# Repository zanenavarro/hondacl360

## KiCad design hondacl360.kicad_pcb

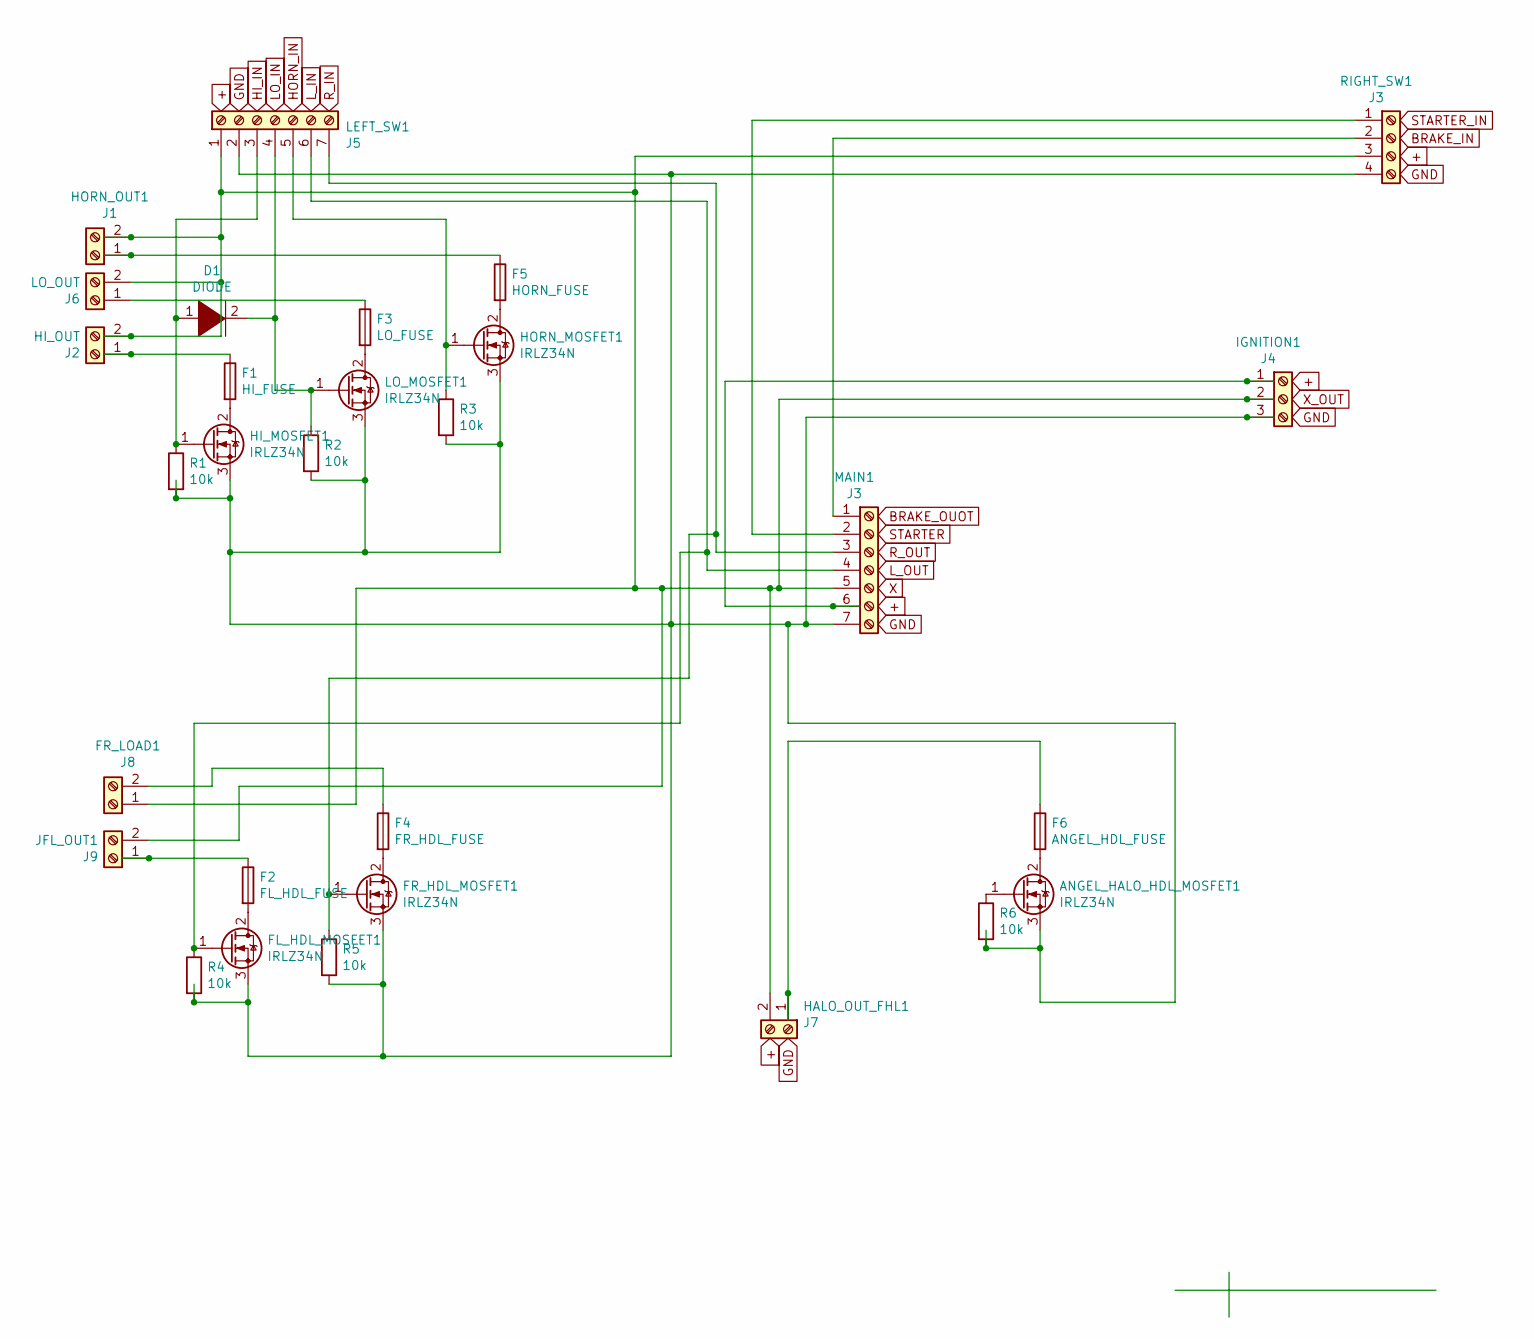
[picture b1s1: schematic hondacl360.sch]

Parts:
ANGEL_HALO_HDL_MOSFET1: IRLZ34N; TO-220-3_Vertical
D1: DIODE; D_DO-35_SOD27_P2.54mm_Vertical_AnodeUp
F1: HI_FUSE; Fuseholder_Blade_Mini_Keystone_3568
F2: FL_HDL_FUSE; Fuseholder_Blade_Mini_Keystone_3568
F3: LO_FUSE; Fuseholder_Blade_Mini_Keystone_3568
F4: FR_HDL_FUSE; Fuseholder_Blade_Mini_Keystone_3568
F5: HORN_FUSE; Fuseholder_Blade_Mini_Keystone_3568
F6: ANGEL_HDL_FUSE; Fuseholder_Blade_Mini_Keystone_3568
FL_HDL_MOSFET1: IRLZ34N; TO-220-3_Vertical
FR_HDL_MOSFET1: IRLZ34N; TO-220-3_Vertical
FR_LOAD1: J8; JST_GH_SM02B-GHS-TB_1x02-1MP_P1.25mm_Horizontal
HALO_OUT_FHL1: J7; JST_GH_SM02B-GHS-TB_1x02-1MP_P1.25mm_Horizontal
HI_MOSFET1: IRLZ34N; TO-220-3_Vertical
HORN_MOSFET1: IRLZ34N; TO-220-3_Vertical
HORN_OUT1: J1; JST_GH_SM02B-GHS-TB_1x02-1MP_P1.25mm_Horizontal
IGNITION1: J4; JST_GH_SM03B-GHS-TB_1x03-1MP_P1.25mm_Horizontal
J2: HI_OUT; JST_GH_SM02B-GHS-TB_1x02-1MP_P1.25mm_Horizontal
J6: LO_OUT; JST_GH_SM02B-GHS-TB_1x02-1MP_P1.25mm_Horizontal
JFL_OUT1: J9; JST_GH_SM02B-GHS-TB_1x02-1MP_P1.25mm_Horizontal
LEFT_SW1: J5; JST_GH_SM07B-GHS-TB_1x07-1MP_P1.25mm_Horizontal
LO_MOSFET1: IRLZ34N; TO-220-3_Vertical
MAIN1: J3; JST_XH_B7B-XH-A_1x07_P2.50mm_Vertical
R1, R2, R3, R4, R5, R6: 10k; R_Axial_DIN0204_L3.6mm_D1.6mm_P2.54mm_Vertical
RIGHT_SW1: J3; JST_GH_SM04B-GHS-TB_1x04-1MP_P1.25mm_Horizontal

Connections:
unnamed: ANGEL_HALO_HDL_MOSFET1.1 (G), R6.1
unnamed: ANGEL_HALO_HDL_MOSFET1.2 (D), F6.2
unnamed: ANGEL_HALO_HDL_MOSFET1.3 (S), FL_HDL_MOSFET1.3 (S), FR_HDL_MOSFET1.3 (S), HI_MOSFET1.3 (S), HORN_MOSFET1.3 (S), IGNITION1.3, LEFT_SW1.2, LO_MOSFET1.3 (S), MAIN1.7, R1.2, R2.2, R3.2, R4.2, R5.2, R6.2, RIGHT_SW1.4
unnamed: D1.1 (K), HI_MOSFET1.1 (G), LEFT_SW1.3, R1.1
unnamed: D1.2 (A), LEFT_SW1.4, LO_MOSFET1.1 (G), R2.1
unnamed: F1.1, J2.1
unnamed: F1.2, HI_MOSFET1.2 (D)
unnamed: F2.1, JFL_OUT1.1
unnamed: F2.2, FL_HDL_MOSFET1.2 (D)
unnamed: F3.1, J6.1
unnamed: F3.2, LO_MOSFET1.2 (D)
unnamed: F4.1, FR_LOAD1.2
unnamed: F4.2, FR_HDL_MOSFET1.2 (D)
unnamed: F5.1, HORN_OUT1.1
unnamed: F5.2, HORN_MOSFET1.2 (D)
unnamed: F6.1, HALO_OUT_FHL1.1
unnamed: FL_HDL_MOSFET1.1 (G), LEFT_SW1.6, MAIN1.4, R4.1
unnamed: FR_HDL_MOSFET1.1 (G), LEFT_SW1.7, MAIN1.3, R5.1
unnamed: FR_LOAD1.1, HALO_OUT_FHL1.2, HORN_OUT1.2, IGNITION1.2, J2.2, J6.2, JFL_OUT1.2, LEFT_SW1.1, MAIN1.5, RIGHT_SW1.3
unnamed: HORN_MOSFET1.1 (G), LEFT_SW1.5, R3.1
unnamed: IGNITION1.1, MAIN1.6
unnamed: MAIN1.1, RIGHT_SW1.2
unnamed: MAIN1.2, RIGHT_SW1.1

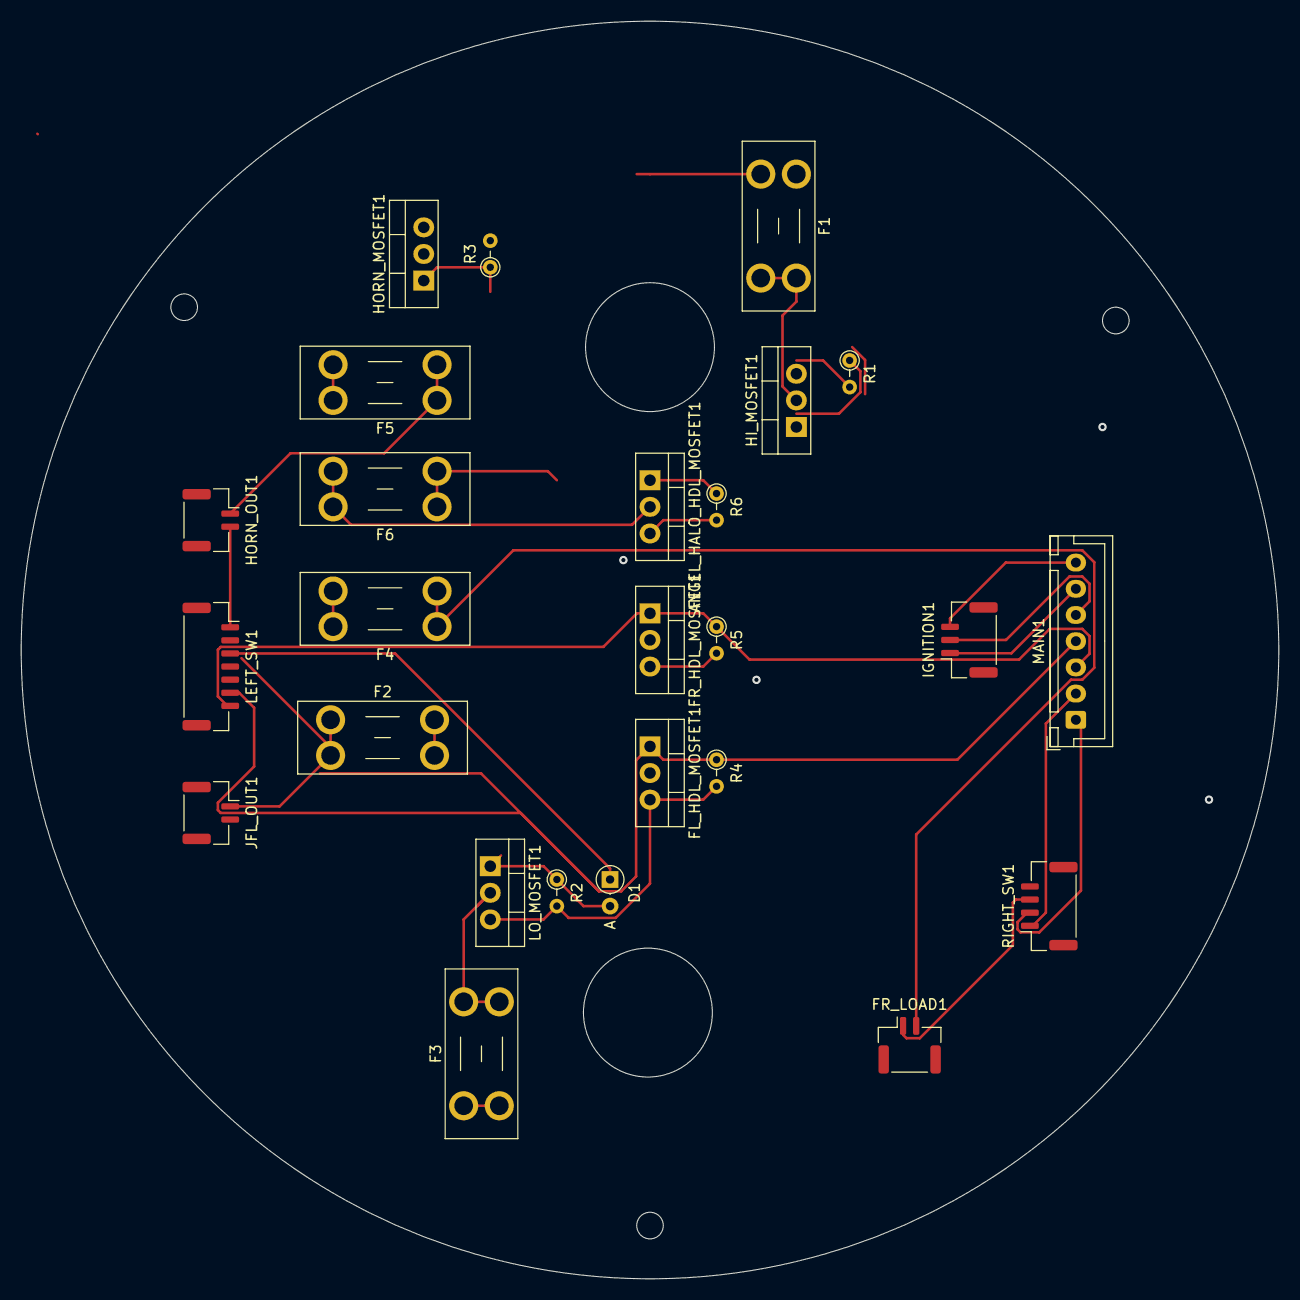
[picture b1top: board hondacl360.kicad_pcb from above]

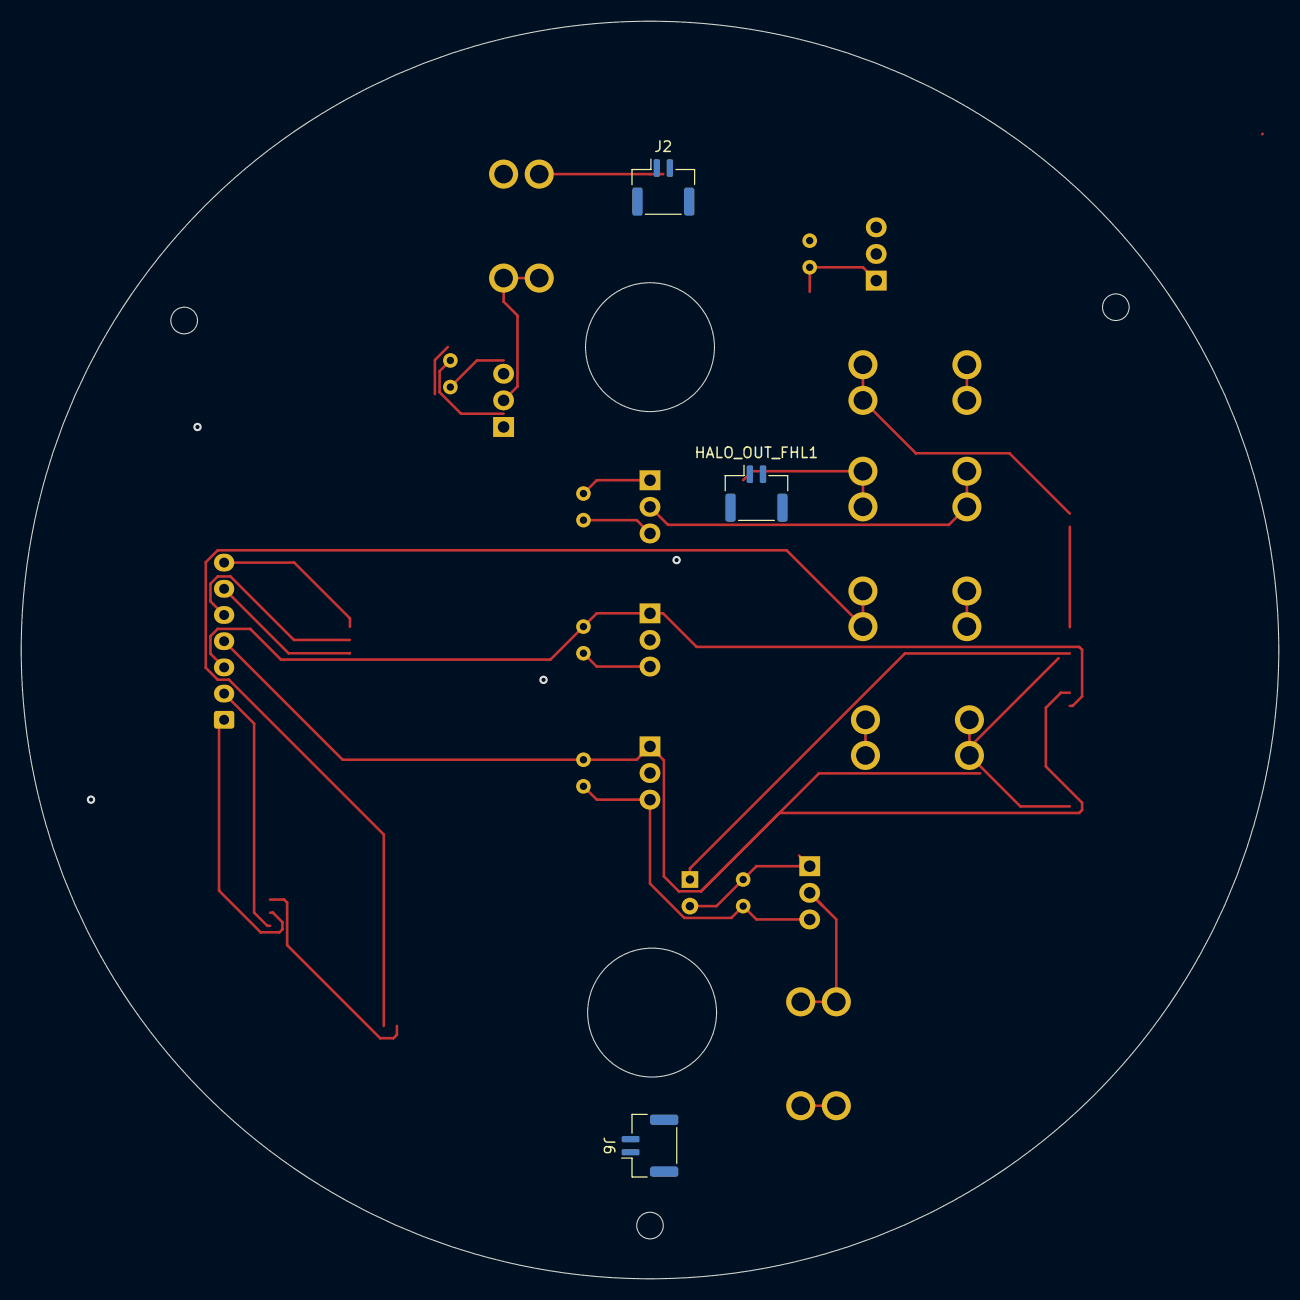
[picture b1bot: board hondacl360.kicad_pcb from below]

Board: 2 copper layers, 120.0 x 120.0 mm, 29 parts (3 on the bottom side), 23 nets.

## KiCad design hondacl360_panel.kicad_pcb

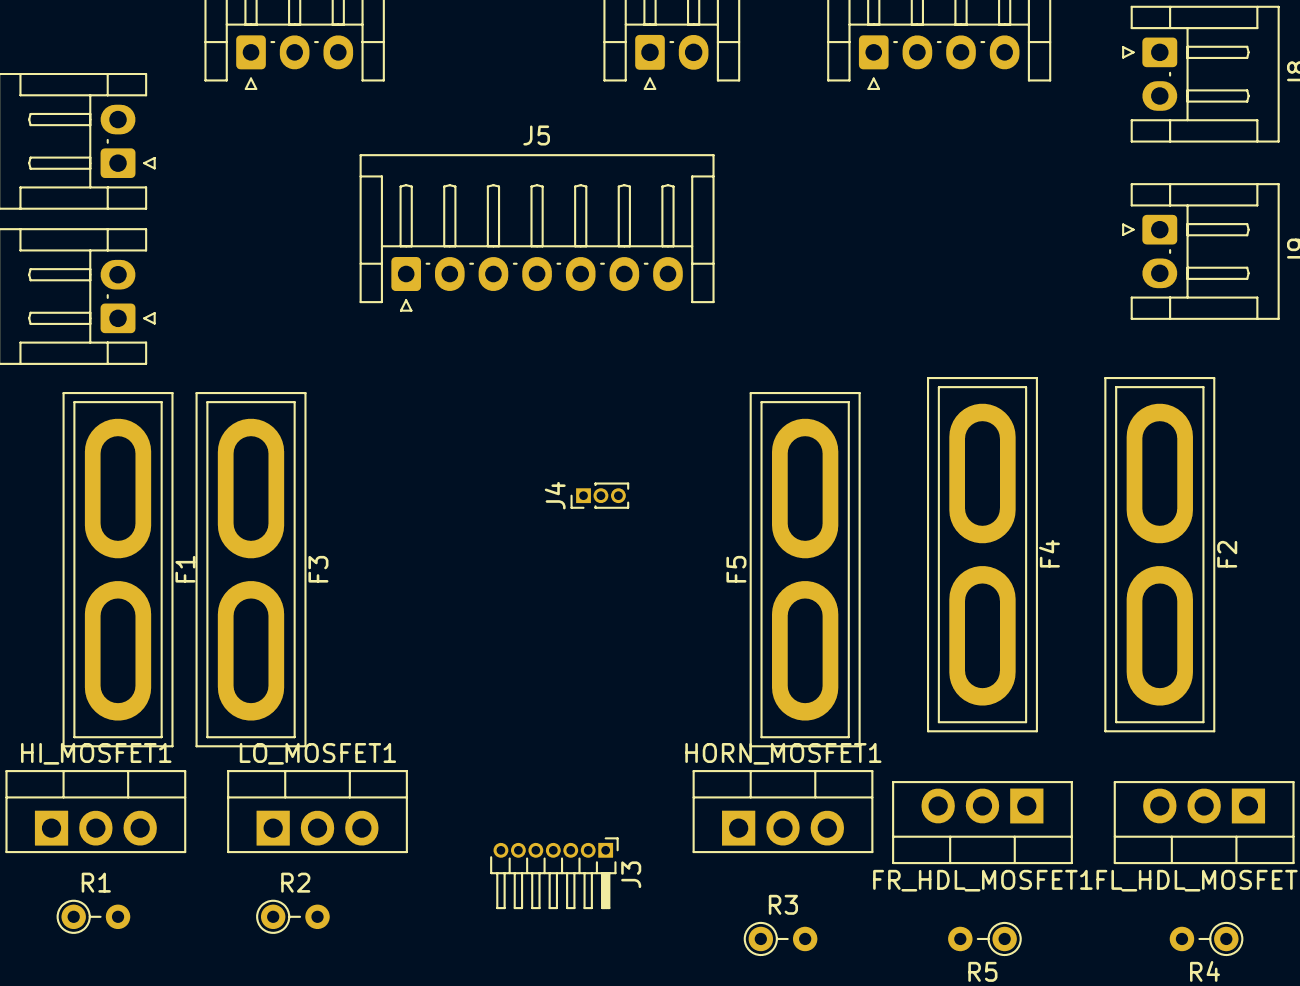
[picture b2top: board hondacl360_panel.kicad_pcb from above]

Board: 2 copper layers, 25 parts (0 on the bottom side), 20 nets.

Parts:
F1, F2, F3, F4, F5: Fuse; Fuse_Blade_ATO_directSolder
FL_HDL_MOSFET1: IRLZ34N; TO-220-3_Vertical
FR_HDL_MOSFET1: IRLZ34N; TO-220-3_Vertical
HI_MOSFET1: IRLZ34N; TO-220-3_Vertical
HORN_MOSFET1: IRLZ34N; TO-220-3_Vertical
J1: HORN_OUT; JST_EH_S2B-EH_1x02_P2.50mm_Horizontal
J2: HI_OUT; JST_EH_S2B-EH_1x02_P2.50mm_Horizontal
J3: MAIN; PinHeader_1x07_P1.00mm_Horizontal
J4: IGNITION; JST_EH_S3B-EH_1x03_P2.50mm_Horizontal
J4#2: RIGHT_SW_IN; PinHeader_1x03_P1.00mm_Vertical
J5: LEFT_SW_IN; JST_EH_S7B-EH_1x07_P2.50mm_Horizontal
J6: LO_OUT; JST_EH_S2B-EH_1x02_P2.50mm_Horizontal
J7: RIGHT_SW; JST_EH_S4B-EH_1x04_P2.50mm_Horizontal
J8: FR_LOAD; JST_EH_S2B-EH_1x02_P2.50mm_Horizontal
J9: FL_LOAD; JST_EH_S2B-EH_1x02_P2.50mm_Horizontal
LO_MOSFET1: IRLZ34N; TO-220-3_Vertical
R1, R2, R3, R4, R5: 10k; R_Axial_DIN0204_L3.6mm_D1.6mm_P2.54mm_Vertical

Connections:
unnamed: F1.1, J2.1
unnamed: F1.2, HI_MOSFET1.2
unnamed: F2.1, J9.1
unnamed: F2.2, FL_HDL_MOSFET1.2
unnamed: F3.1, J6.1
unnamed: F3.2, LO_MOSFET1.2
unnamed: F4.1, J8.1
unnamed: F4.2, FR_HDL_MOSFET1.2
unnamed: F5.1, J1.1
unnamed: F5.2, HORN_MOSFET1.2
unnamed: FL_HDL_MOSFET1.1, J3.3, J5.7, R4.1
unnamed: FL_HDL_MOSFET1.3, FR_HDL_MOSFET1.3, HI_MOSFET1.3, HORN_MOSFET1.3, J3.7, J4.3, J5.2, J7.4, LO_MOSFET1.3, R1.2, R2.2, R3.2, R4.2, R5.2
unnamed: FR_HDL_MOSFET1.1, J3.2, J5.6, R5.1
unnamed: HI_MOSFET1.1, J5.3, R1.1
unnamed: HORN_MOSFET1.1, J5.5, R3.1
unnamed: J1.2, J2.2, J3.5, J4.2, J5.1, J6.2, J7.3, J8.2, J9.2
unnamed: J3.1, J4#2.2, J7.2
unnamed: J3.4, J4#2.1, J7.1
unnamed: J3.6, J4.1
unnamed: J5.4, LO_MOSFET1.1, R2.1

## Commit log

2024-08-22 First Commit :{)
2024-08-23 [hondacl360]: first commit
